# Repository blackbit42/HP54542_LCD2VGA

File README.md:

# Conversion of HP 54520C / 54540C oscilloscopes to VGA display(s)

The HP 54520C / 54540C series of oscilloscopes is equipped with color LCD displays, in contrast to their non-C predecessors which had monochrome CRT displays. While the multi-color display is nice in principle, the LCDs that were used unfortunately commonly failed. Those scopes are still quite capable by 2023 standards, hence worth preserving. The content of this repository is a conversion of the scope to VGA through a FPGA bitstream and a PCB design that is using an [UPduino](https://tinyvision.ai/products/upduino-v3-1) as a daughterboard.

Pretty much the same hack has been done before by [Adil Malik](https://hackaday.com/2017/06/01/fpga-rescues-scope-from-the-dumpster/), though now FPGA and PCB designs are made available for other people to reproduce.

# Implementation details

The PCB is designed to have mounting holes placed in distance to be compatible with [VESA MIS-D (75x75)](https://en.wikipedia.org/wiki/Flat_Display_Mounting_Interface), which allows the PCB to be mounted sturdily at the backside of the used VGA TFT inside the scope.

Hirose DF13 connectors are stipulated on the PCB so that the original LCD cables don't have to be modified.

The PCB and UPduino are powered from the LCD connections. The VGA TFT is powered from the scope PSU.

The entire modification of the instrument is non-invasive and can be undone if desired.

## Findings

HP decided to mount the LCD panel upside down. Probably as that was convenient is regards to the position of the connectors. An implication of that is that the internal VGGA monitor is mounted upside down as well (which doesn't make a difference really) and that an external monitor must be rotated as well. If one would desire to change that, a frame buffer must be implemented in the FPGA, which isn't hard to do but required more RAM than the UPduino has.

## Errata

Rev.1 of the PCB design contains an error. The footprint for the UPduino is 0.2" too narrow. I fixed this with infamous offset-pinheaders of shame. Keep this in mind if you intend to get a PCB produced. Patches welcome :-)

## PCBs

As of 10 Jan 2023 I have some spare PCBs in stock. Get in touch via the email address I've used for the commits if you want one.

## Pictures

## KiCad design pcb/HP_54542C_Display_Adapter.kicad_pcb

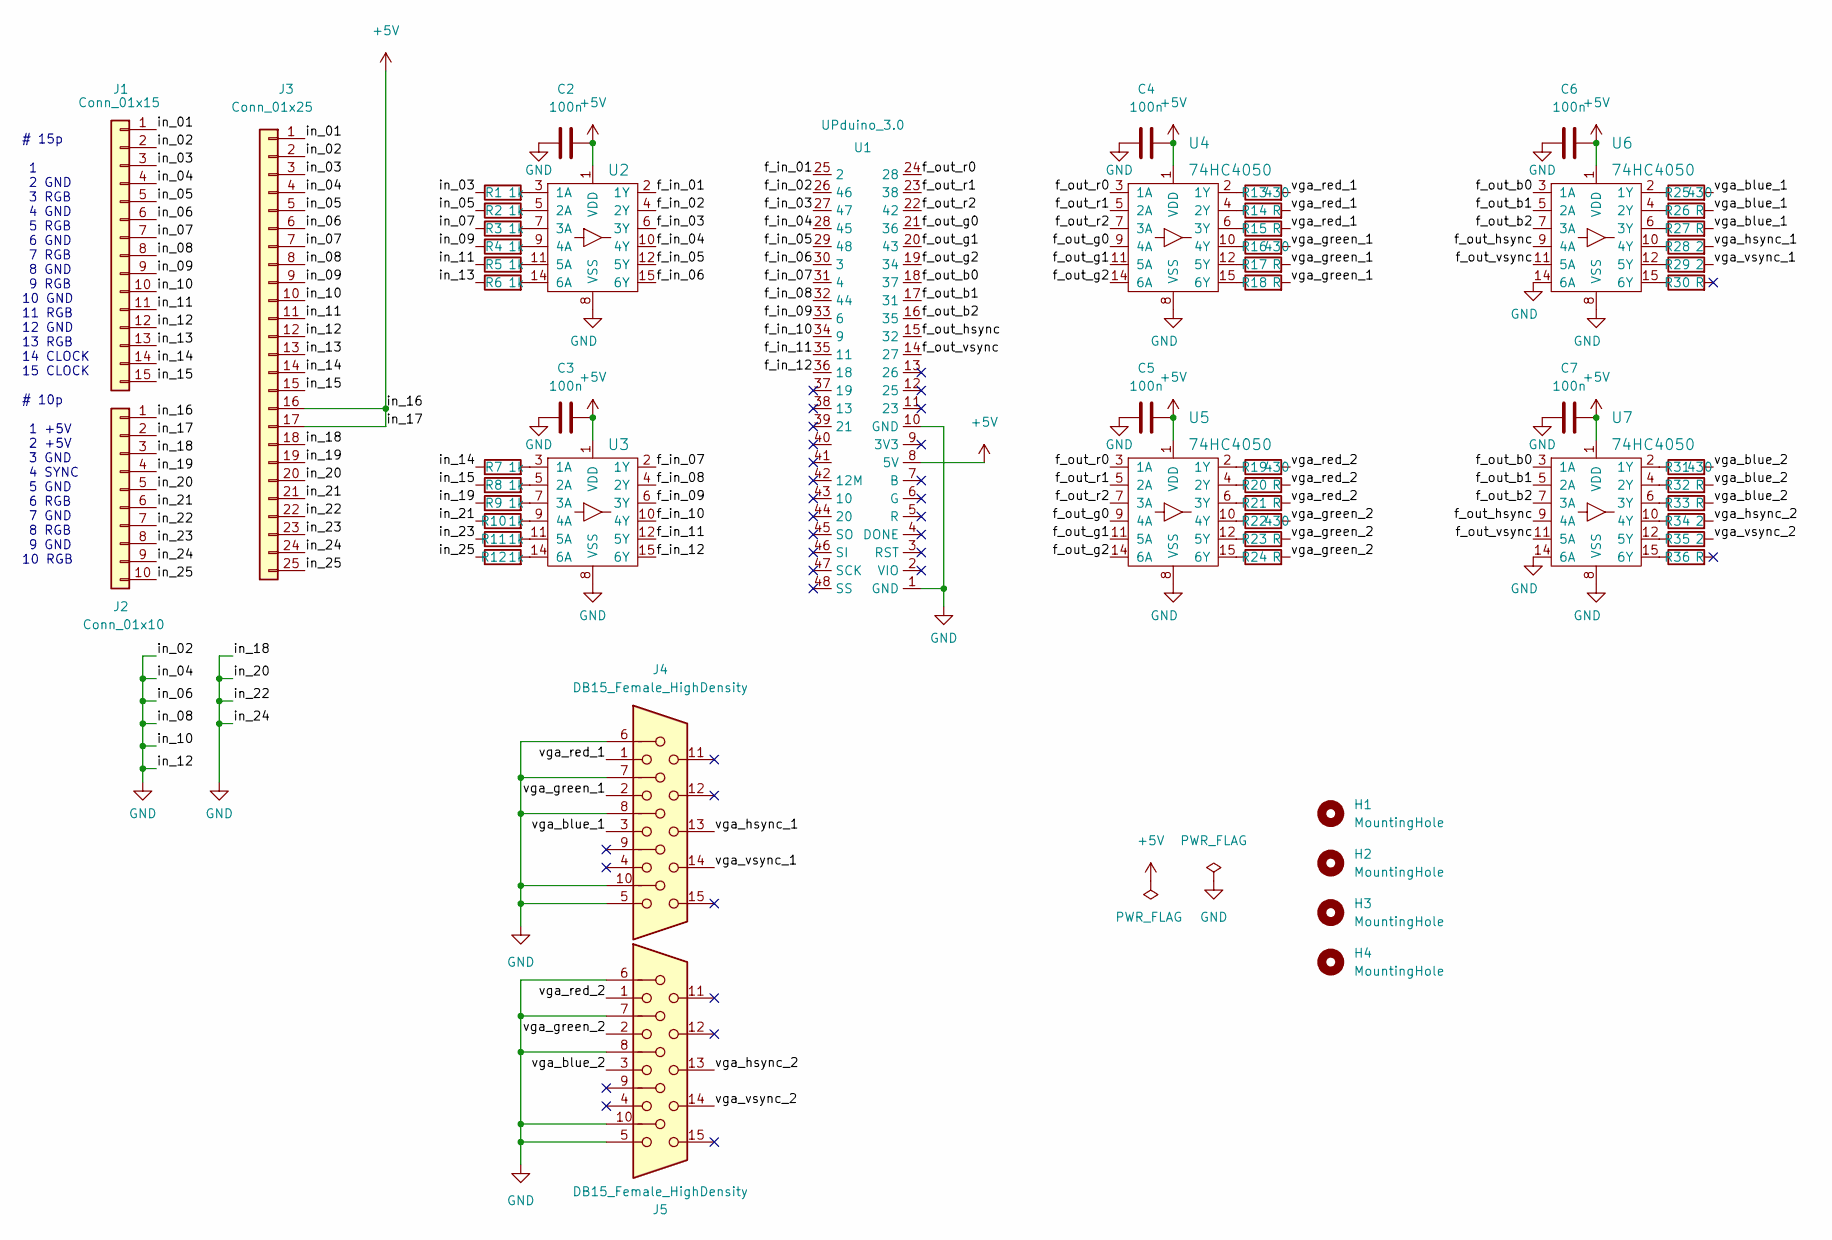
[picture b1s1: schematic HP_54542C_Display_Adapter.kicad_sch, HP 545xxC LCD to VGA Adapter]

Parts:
C2, C3, C4, C5, C6, C7: 100n; C_0603_1608Metric_Pad1.08x0.95mm_HandSolder; LCSC C14663
H1, H2, H3, H4: MountingHole; MountingHole_4.3mm_M4_DIN965_Pad
J1: Conn_01x15; PinSocket_1x15_P1.27mm_Vertical
J2: Conn_01x10; PinSocket_1x10_P1.27mm_Vertical
J3: Conn_01x25; PinHeader_1x25_P2.54mm_Vertical
J4, J5: DB15_Female_HighDensity; VGA
R1, R2, R3, R4, R5, R6, R7, R8, R9, R10, R11, R12: 1k; R_0603_1608Metric_Pad0.98x0.95mm_HandSolder; LCSC C21190
R13, R16, R19, R22, R25, R31: 430; R_0603_1608Metric_Pad0.98x0.95mm_HandSolder; LCSC C23170
R14, R15, R17, R18, R20, R21, R23, R24, R26, R27, R30, R32, R33, R36: R; R_0603_1608Metric_Pad0.98x0.95mm_HandSolder
R28, R29, R34, R35: 2; R_0603_1608Metric_Pad0.98x0.95mm_HandSolder; LCSC C22977
U1: UPduino_3.0; DIP-48_W15.24mm_LongPads
U2, U3, U4, U5, U6, U7: 74HC4050; DIP-16_W7.62mm_LongPads

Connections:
+5V: C2.2, C3.2, C4.2, C5.2, C6.2, C7.2, J2.1, J2.2, J3.16, J3.17, U1.8 (5V), U2.1 (VDD), U3.1 (VDD), U4.1 (VDD), U5.1 (VDD), U6.1 (VDD), U7.1 (VDD)
/f_in_01: U1.25 (2), U2.2 (1Y)
/f_in_02: U1.26 (46), U2.4 (2Y)
/f_in_03: U1.27 (47), U2.6 (3Y)
/f_in_04: U1.28 (45), U2.10 (4Y)
/f_in_05: U1.29 (48), U2.12 (5Y)
/f_in_06: U1.30 (3), U2.15 (6Y)
/f_in_07: U1.31 (4), U3.2 (1Y)
/f_in_08: U1.32 (44), U3.4 (2Y)
/f_in_09: U1.33 (6), U3.6 (3Y)
/f_in_10: U1.34 (9), U3.10 (4Y)
/f_in_11: U1.35 (11), U3.12 (5Y)
/f_in_12: U1.36 (18), U3.15 (6Y)
/f_out_b0: U1.18 (37), U6.3 (1A), U7.3 (1A)
/f_out_b1: U1.17 (31), U6.5 (2A), U7.5 (2A)
/f_out_b2: U1.16 (35), U6.7 (3A), U7.7 (3A)
/f_out_g0: U1.21 (36), U4.9 (4A), U5.9 (4A)
/f_out_g1: U1.20 (43), U4.11 (5A), U5.11 (5A)
/f_out_g2: U1.19 (34), U4.14 (6A), U5.14 (6A)
/f_out_hsync: U1.15 (32), U6.9 (4A), U7.9 (4A)
/f_out_r0: U1.24 (28), U4.3 (1A), U5.3 (1A)
/f_out_r1: U1.23 (38), U4.5 (2A), U5.5 (2A)
/f_out_r2: U1.22 (42), U4.7 (3A), U5.7 (3A)
/f_out_vsync: U1.14 (27), U6.11 (5A), U7.11 (5A)
/in_01: J1.1, J3.1
/in_03: J1.3, J3.3, R1.1
/in_05: J1.5, J3.5, R2.1
/in_07: J1.7, J3.7, R3.1
/in_09: J1.9, J3.9, R4.1
/in_11: J1.11, J3.11, R5.1
/in_13: J1.13, J3.13, R6.1
/in_14: J1.14, J3.14, R7.1
/in_15: J1.15, J3.15, R8.1
/in_19: J2.4, J3.19, R9.1
/in_21: J2.6, J3.21, R10.1
/in_23: J2.8, J3.23, R11.1
/in_25: J2.10, J3.25, R12.1
/vga_blue_1: J4.3, R25.2, R26.2, R27.2
/vga_blue_2: J5.3, R31.2, R32.2, R33.2
/vga_green_1: J4.2, R16.2, R17.2, R18.2
/vga_green_2: J5.2, R22.2, R23.2, R24.2
/vga_hsync_1: J4.13, R28.2
/vga_hsync_2: J5.13, R34.2
/vga_red_1: J4.1, R13.2, R14.2, R15.2
/vga_red_2: J5.1, R19.2, R20.2, R21.2
/vga_vsync_1: J4.14, R29.2
/vga_vsync_2: J5.14, R35.2
GND: C2.1, C3.1, C4.1, C5.1, C6.1, C7.1, J1.2, J1.4, J1.6, J1.8, J1.10, J1.12, J2.3, J2.5, J2.7, J2.9, J3.2, J3.4, J3.6, J3.8, J3.10, J3.12, J3.18, J3.20, J3.22, J3.24, J4.5, J4.6, J4.7, J4.8, J4.10, J5.5, J5.6, J5.7, J5.8, J5.10, U1.1 (GND), U1.10 (GND), U2.8 (VSS), U3.8 (VSS), U4.8 (VSS), U5.8 (VSS), U6.8 (VSS), U6.14 (6A), U7.8 (VSS), U7.14 (6A)
unnamed: R1.2, U2.3 (1A)
unnamed: R2.2, U2.5 (2A)
unnamed: R3.2, U2.7 (3A)
unnamed: R4.2, U2.9 (4A)
unnamed: R5.2, U2.11 (5A)
unnamed: R6.2, U2.14 (6A)
unnamed: R7.2, U3.3 (1A)
unnamed: R8.2, U3.5 (2A)
unnamed: R9.2, U3.7 (3A)
unnamed: R10.2, U3.9 (4A)
unnamed: R11.2, U3.11 (5A)
unnamed: R12.2, U3.14 (6A)
unnamed: R13.1, U4.2 (1Y)
unnamed: R14.1, U4.4 (2Y)
unnamed: R15.1, U4.6 (3Y)
unnamed: R16.1, U4.10 (4Y)
unnamed: R17.1, U4.12 (5Y)
unnamed: R18.1, U4.15 (6Y)
unnamed: R19.1, U5.2 (1Y)
unnamed: R20.1, U5.4 (2Y)
unnamed: R21.1, U5.6 (3Y)
unnamed: R22.1, U5.10 (4Y)
unnamed: R23.1, U5.12 (5Y)
unnamed: R24.1, U5.15 (6Y)
unnamed: R25.1, U6.2 (1Y)
unnamed: R26.1, U6.4 (2Y)
unnamed: R27.1, U6.6 (3Y)
unnamed: R28.1, U6.10 (4Y)
unnamed: R29.1, U6.12 (5Y)
unnamed: R30.1, U6.15 (6Y)
unnamed: R31.1, U7.2 (1Y)
unnamed: R32.1, U7.4 (2Y)
unnamed: R33.1, U7.6 (3Y)
unnamed: R34.1, U7.10 (4Y)
unnamed: R35.1, U7.12 (5Y)
unnamed: R36.1, U7.15 (6Y)

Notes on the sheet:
# 15p 1 2 GND 3 RGB 4 GND 5 RGB 6 GND 7 RGB 8 GND 9 RGB 10 GND 11 RGB 12 GND 13 RGB 14 CLOCK 15 CLOCK # 10p 1 +5V 2 +5V 3 GND 4 SYNC 5 GND 6 RGB 7 GND 8 RGB 9 GND 10 RGB

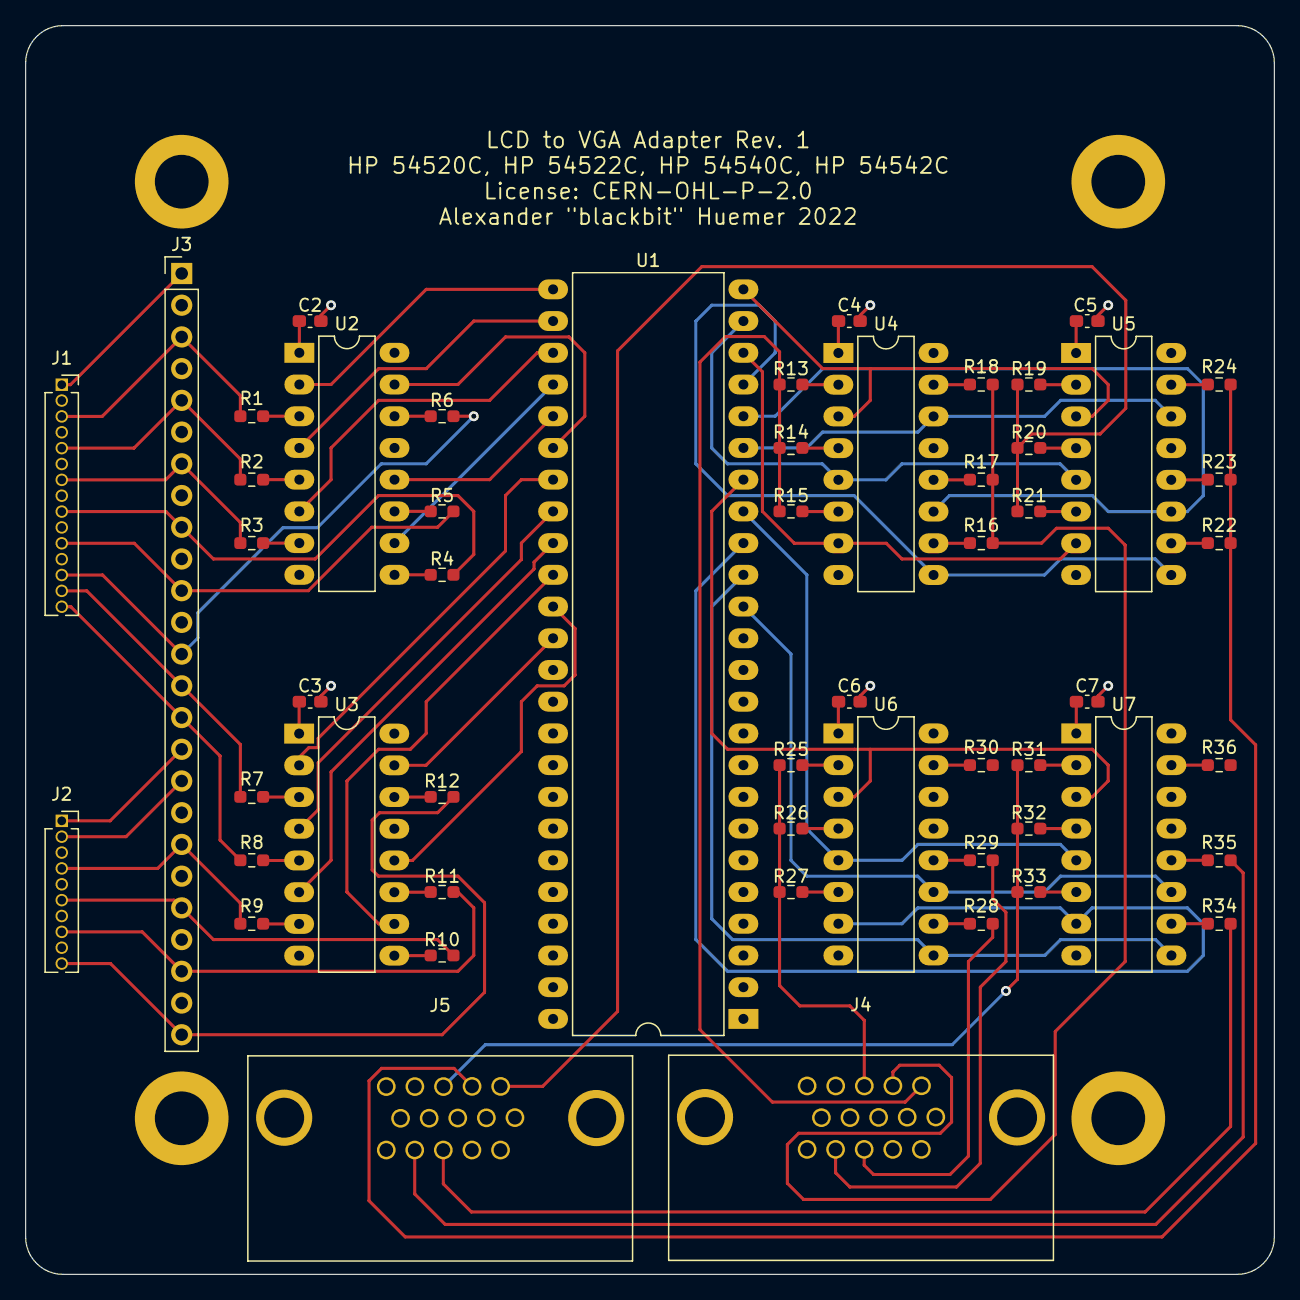
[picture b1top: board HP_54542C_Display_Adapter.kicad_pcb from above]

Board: 4 copper layers, 100.0 x 100.0 mm, 58 parts (0 on the bottom side), 84 nets.

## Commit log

2021-01-01 root-commit
2021-01-01 write logfiles
2021-01-01 rename HP54542C_LCD_to_VGA -> HP54542C_LCD2VGA
2021-01-01 add output wires for [hv]sync and adjust .pcf
2021-01-02 turn all LEDs off
2021-01-03 got picture, but horizontally offset and intermittent
2021-01-04 cleanup
2022-02-23 ignore *.svg
2022-02-23 ignore *.png
2022-02-23 ignore obj_dir/
2022-02-23 add .vimrc for verilator
2022-02-23 design works!
2022-02-23 ignore *.vcd
2023-01-10 add kicad design
2023-01-10 icestick -> upduino
2023-01-10 move fpga design to subfolder
2023-01-13 add README.md for github

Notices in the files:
pcb/HP_54542C_Display_Adapter.kicad_pcb:
License: CERN-OHL-P-2.0
